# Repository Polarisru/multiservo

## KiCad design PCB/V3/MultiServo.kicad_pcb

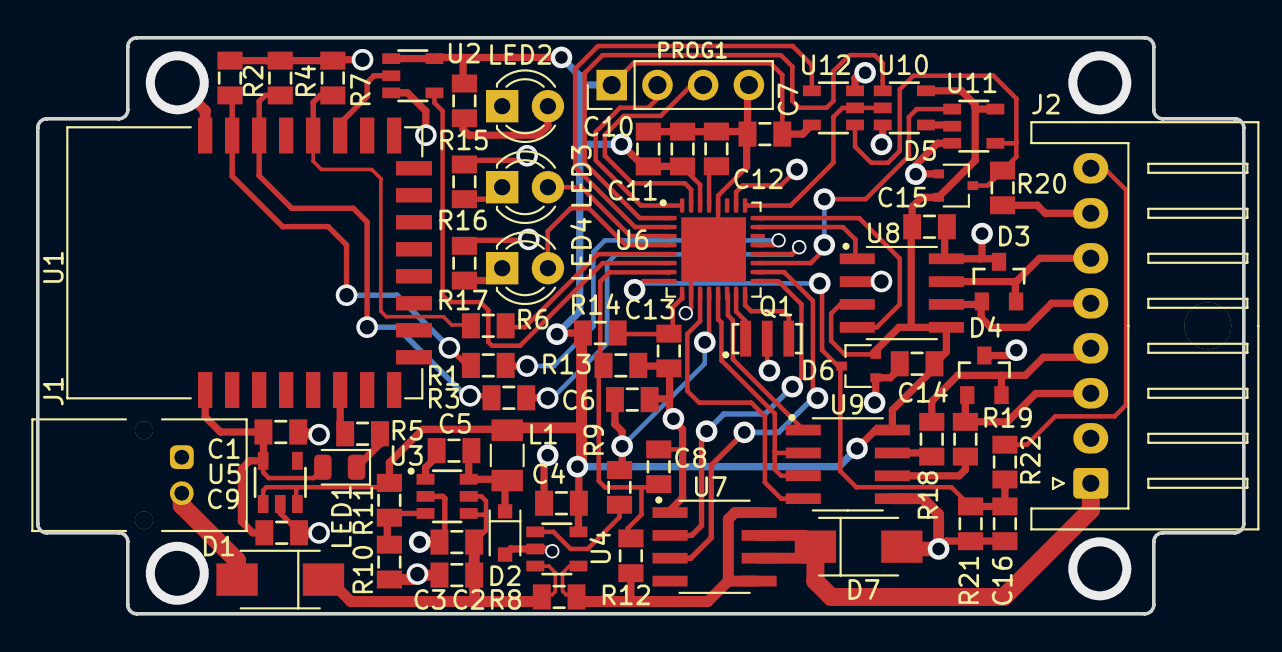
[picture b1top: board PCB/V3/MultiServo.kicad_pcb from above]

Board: 2 copper layers, 67.0 x 32.0 mm, 66 parts (0 on the bottom side), 56 nets.

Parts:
C1, C10, C12, C13: 1.0; C0805
C2: 2.2; C0805
C3, C4, C5, C6, C8, C11, C14, C15, C16: 0.1; C0805
C7, C9: 22.0; C0805
D1: VSSAF5L45; D_SMA
D2: BAT165; D_SOD-323
D3, D4: NUP2105L; SOT23-3
D5, D6: BAT54SW; SOT-323_SC-70
D7: SMA6F30A; D_SMA
J1: JST_S02B_PASK; JST_S02B-PASK-2LFSN_1x02
J2: S08B-XASK-1; JST_XA_S08B-XASK-1x08_P2.50mm_Horizontal
L1: 10uH; L_1206
LED1: RED; LED_0805_2012Metric
LED2: GREEN; LED_D3.0mm
LED3: BLUE; LED_D3.0mm
LED4: RED; LED_D3.0mm
PROG1: 01x04; PinHeader_1x04_P2.54mm_Vertical
Q1: 16MHz; RES-3
R1, R3, R5, R6, R9, R15, R16, R17, R20: 1k; R0805
R2, R4, R7: 2k; R0805
R8: 0.02; R0805
R10: 4k3; R0805
R11: 22k; R0805
R12: 100k; R0805
R13: 15k; R0805
R14: 10; R0805
R18, R19: 100; R0805
R21, R22: 10k; R0805
U1: JDY-08
U2, U11: SN74LV1T126; SOT23-5
U3: MP2459; SOT23-6
U4: INA195A; SOT23-5
U5: MIC5504-3.3; SOT23-5
U6: ATSAMC21E18A-MUT; QFN-32-1EP_5x5mm_P0.5mm_EP3.6x3.6mm
U7: VN750PS; SOIC-8_3.9x4.9mm_P1.27mm
U8: MCP2542FDT-SN; SOIC-8_3.9x4.9mm_P1.27mm
U9: THVD1500; SOIC-8_3.9x4.9mm_P1.27mm
U10, U12: SN74LVC1G86; SOT23-5

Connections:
+3V3: C1.1, C9.2, LED1.2, U1.1, U5.5
+5V: C4.2, C7.2, C10.1, C11.1, C14.1, C15.1, D5.2, D6.2, L1.2, PROG1.1, R11.1, R14.2, R15.2, U2.1, U2.5, U4.5, U5.1, U5.3, U6.30, U8.3, U8.5, U9.8, U10.5, U11.5, U12.5
/485_A: D4.1, J2.3, R19.1
/485_B: D4.2, J2.4, R18.1
/485_DIR: U6.13, U9.2, U9.3
/485_RX: U6.14, U9.1
/485_TX: U6.11, U9.4
/ADC_FB: C16.2, D6.3, R21.2, R22.2, U6.8
/ADC_I: C6.2, R9.1, U6.12
/ADC_U: C8.2, R12.2, R13.1, U6.7
/BT_RX: U2.4, U6.6
/BT_TX: R6.1, U6.5
/CANH: D3.2, J2.6, U8.7
/CANL: D3.1, J2.5, U8.6
/CAN_RX: U6.24, U8.4
/CAN_TX: U6.23, U8.1
/LED1: LED3.2, U6.3
/LED2: LED4.2, U6.4
/POWER: C2.2, C3.2, D1.1, R8.2, U3.4, U3.5, U4.3
/PWM_FB: J2.8, R22.1
/PWRC: R3.2, U6.20
/RES: R1.2, U6.21
/S.BUS: J2.7, R20.1
/SBUSPOL: U6.25, U10.2, U12.2
/SBUSRX: U6.2, U12.4
/SBUSTE: U6.19, U11.1
/SBUSTX: U6.1, U10.1
/SERVO+: D7.1, J2.1, U7.6, U7.7
/SERVO_ON: U6.17, U7.2
/STATUS: U6.18, U7.3
/SWCLK: PROG1.3, U6.31
/SWDIO: PROG1.2, U6.32
GND: C1.2, C2.1, C3.1, C4.1, C6.1, C7.1, C8.1, C9.1, C10.2, C11.2, C12.2, C13.2, C14.2, C15.2, C16.1, D2.2, D3.3, D4.3, D5.1, D6.1, D7.2, J1.1, J2.2, LED2.1, PROG1.4, Q1.2, R2.1, R4.1, R7.1, R10.2, R13.2, R16.1, R17.1, R21.1, U1.24, U2.3, U3.2, U4.2, U5.2, U6.10, U6.28, U6.EP, U7.1, U8.2, U8.8, U9.5, U10.3, U11.3, U12.3
unnamed: C5.1, U3.1
unnamed: C5.2, D2.1, L1.1, U3.6
unnamed: C12.1, U6.29
unnamed: C13.1, R14.1, U6.9
unnamed: D1.2, J1.2
unnamed: D5.3, R20.2, U11.4, U12.1
unnamed: LED1.1, R5.1
unnamed: LED2.2, R15.1
unnamed: LED3.1, R16.2
unnamed: LED4.1, R17.2
unnamed: Q1.1, U6.15
unnamed: Q1.3, U6.16
unnamed: R1.1, R2.2, U1.23
unnamed: R3.1, R4.2, U1.22
unnamed: R5.2, U1.6
unnamed: R6.2, R7.2, U1.20
unnamed: R9.2, U4.1
unnamed: R10.1, R11.2, U3.3
unnamed: R8.1, R12.1, U4.4, U7.5, U7.8
unnamed: R18.2, U9.7
unnamed: R19.2, U9.6
unnamed: U1.19, U2.2
unnamed: U10.4, U11.2

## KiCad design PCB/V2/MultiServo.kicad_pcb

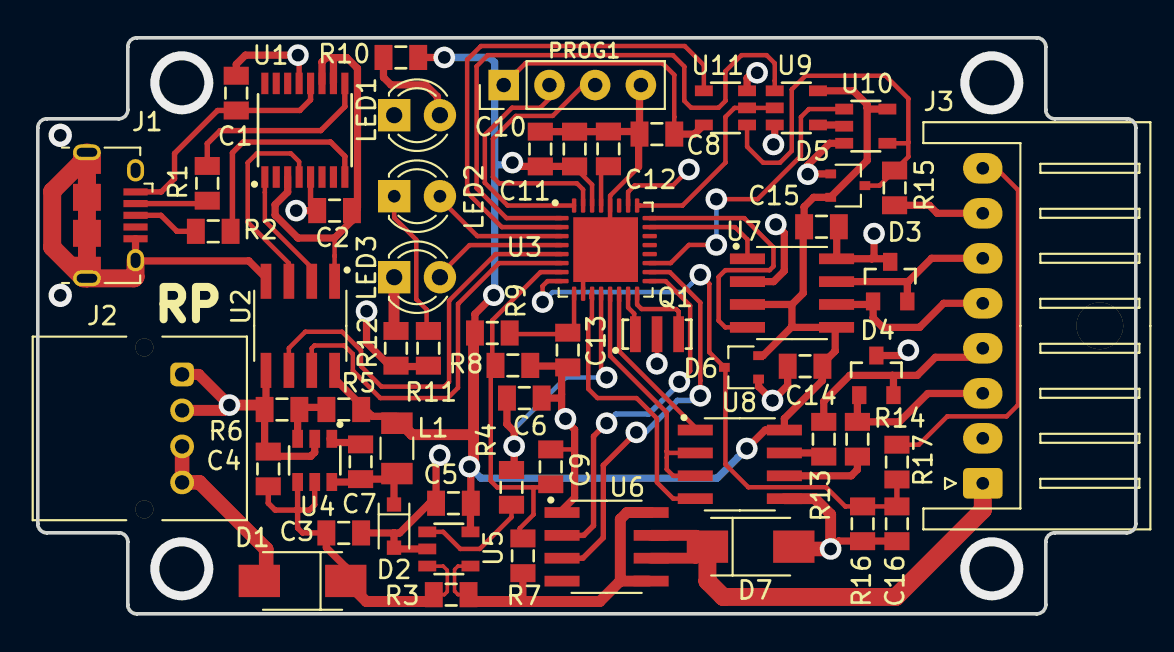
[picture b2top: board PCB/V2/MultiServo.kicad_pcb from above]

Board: 2 copper layers, 61.0 x 32.0 mm, 60 parts (0 on the bottom side), 56 nets.

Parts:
C1, C3: 2.2; C0805
C2, C10, C12, C13: 1.0; C0805
C4, C5, C6, C7, C9, C11, C14, C15, C16: 0.1; C0805
C8: 22.0; C0805
D1: VSSAF5L45; D_SMA
D2: BAT165; D_SOD-323
D3, D4: NUP2105L; SOT23-3
D5, D6: BAT54SW; SOT-323_SC-70
D7: SMA6F30A; D_SMA
J1: USB_B_Micro; USB_Micro-B_Amphenol_10118194_Horizontal
J2: S04B; JST_S04B-PASK-2LFSN_1x04
J3: S08B-XASK-1; JST_XA_S08B-XASK-1x08_P2.50mm_Horizontal
L1: 10uH; L_1206
LED1: GREEN; LED_D3.0mm
LED2: BLUE; LED_D3.0mm
LED3: RED; LED_D3.0mm
PROG1: 01x04; PinHeader_1x04_P2.54mm_Vertical
Q1: 16MHz; RES-3
R1, R2: 27; R0805
R3: 0.02; R0805
R4, R10, R11, R12, R15: 1k; R0805
R5: 22k; R0805
R6: 4k3; R0805
R7: 100k; R0805
R8: 15k; R0805
R9: 10; R0805
R13, R14: 100; R0805
R16, R17: 10k; R0805
U1: FT230XS; SSOP-16_3.9x4.9mm_P0.635mm
U2: Si8621BC; SOIC-8_3.9x4.9mm_P1.27mm
U3: ATSAMC21E18A-MUT; QFN-32-1EP_5x5mm_P0.5mm_EP3.6x3.6mm
U4: MP2459; SOT23-6
U5: INA195A; SOT23-5
U6: VN750PS; SOIC-8_3.9x4.9mm_P1.27mm
U7: MCP2542FDT-SN; SOIC-8_3.9x4.9mm_P1.27mm
U8: THVD1500; SOIC-8_3.9x4.9mm_P1.27mm
U9, U11: SN74LVC1G86; SOT23-5
U10: SN74LV1T126; SOT23-5

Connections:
+5V: C5.2, C8.2, C10.1, C11.1, C14.1, C15.1, D5.2, D6.2, L1.2, PROG1.1, R5.1, R9.2, R10.2, U2.8, U3.30, U5.5, U7.3, U7.5, U8.8, U9.5, U10.5, U11.5
/485_A: D4.1, J3.3, R14.1
/485_B: D4.2, J3.4, R13.1
/485_DIR: U3.13, U8.2, U8.3
/485_RX: U3.14, U8.1
/485_TX: U3.11, U8.4
/ADC_FB: C16.2, D6.3, R16.2, R17.2, U3.8
/ADC_I: C6.2, R4.1, U3.12
/ADC_U: C9.2, R7.2, R8.1, U3.7
/CANH: D3.2, J3.6, U7.7
/CANL: D3.1, J3.5, U7.6
/CAN_RX: U3.24, U7.4
/CAN_TX: U3.23, U7.1
/LED1: LED2.2, U3.3
/LED2: LED3.2, U3.4
/POWER: C3.2, C4.2, D1.1, R3.2, U4.4, U4.5, U5.3
/PWM_FB: J3.8, R17.1
/S.BUS: J3.7, R15.1
/SBUSPOL: U3.25, U9.2, U11.2
/SBUSRX: U3.2, U11.4
/SBUSTE: U3.19, U10.1
/SBUSTX: U3.1, U9.1
/SERVO+: D7.1, J3.1, U6.6, U6.7
/SERVO_ON: U3.17, U6.2
/STATUS: U3.18, U6.3
/SWCLK: PROG1.3, U3.31
/SWDIO: PROG1.2, U3.32
/USB_GND: C1.1, C2.2, J1.5, J1.6, U1.5, U1.13, U2.4
/USB_RX: U2.7, U3.6
/USB_TX: U2.6, U3.5
GND: C3.1, C4.1, C5.1, C6.1, C8.1, C9.1, C10.2, C11.2, C12.2, C13.2, C14.2, C15.2, C16.1, D2.2, D3.3, D4.3, D5.1, D6.1, D7.2, J2.1, J2.2, J3.2, LED1.1, PROG1.4, Q1.2, R6.2, R8.2, R11.1, R12.1, R16.1, U2.5, U3.10, U3.28, U3.EP, U4.2, U5.2, U6.1, U7.2, U7.8, U8.5, U9.3, U10.3, U11.3
unnamed: C1.2, J1.1, U1.12
unnamed: C2.1, U1.3, U1.10, U1.11, U2.1
unnamed: C7.1, U4.1
unnamed: C7.2, D2.1, L1.1, U4.6
unnamed: C12.1, U3.29
unnamed: C13.1, R9.1, U3.9
unnamed: D1.2, J2.3, J2.4
unnamed: D5.3, R15.2, U10.4, U11.1
unnamed: J1.2, R1.2
unnamed: J1.3, R2.2
unnamed: LED1.2, R10.1
unnamed: LED2.1, R11.2
unnamed: LED3.1, R12.2
unnamed: Q1.1, U3.15
unnamed: Q1.3, U3.16
unnamed: R1.1, U1.9
unnamed: R2.1, U1.8
unnamed: R3.1, R7.1, U5.4, U6.5, U6.8
unnamed: R4.2, U5.1
unnamed: R5.2, R6.1, U4.3
unnamed: R13.2, U8.7
unnamed: R14.2, U8.6
unnamed: U1.1, U2.2
unnamed: U1.4, U2.3
unnamed: U9.4, U10.2

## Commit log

2020-12-20 New modules added from SPAN, compilation successful, but many functions need to be updated
2020-12-22 KeeLoq is not working yet
2020-12-22 Schematics is new
2020-12-22 Software for bootloading added (Lazarus) Bootloader from LS1 project added, must be changed for ATSAMC21 Keeloq receiving via TCC capture is working, but must be improved for real life
2020-12-23 PWM is working, Analog module started, outputs working, communication working
2020-12-23 Working on RS485 and CAN
2020-12-28 RS485 servo is supported EEPROM settings are working Bootloader is working
2020-12-31 KeeLoq is working now CAN is also working
2021-01-01 3D models added Supply voltage and current calibration are working Problem with voltage measurement fixed Updater is working
2021-01-01 pyVisio directory added
2021-01-02 Connection, position, readout of U/I/t° is working ToDo: Read parameters, check for bugs
2021-01-03 Write/read parameters is not ready
2021-01-03 main.py added
2021-01-03 Generated Hex file added to repository
2021-01-18 feat: Channels for ADC added, current is ADC1 now
2021-01-19 ADC DMA added Drivers moved to drivers.h
2021-01-20 Working on SBUS
2021-01-22 PCBs added for both USB and BT
2021-01-31 Futaba is working now, but additional thread is needed. Fast analog channel with DMA is working now. Some new HW files added.
2021-02-01 Current graph readout added (GBx) Graph added to pyvisio
2021-02-02 FFT added to current graph
2021-02-03 SBUS has own task and transferred via DMA
2021-02-04 Libcanard added Full SBUS support now Problem with ADC0 solved, but needs to be cleared
2021-02-16 - Meteor protocol started - UAVCAN v0 files added - PWM frequency is 100Hz now - FFT added, but not working properly
2021-02-24 3d model for bottom changed for new PCB
2021-02-24 3d model for new PCB added
2021-02-24 3d model for cover added for new PCB
2021-02-28 HW: Cover changed to fix LEDs position
2021-03-02 FW: - Simple JDY-08 initialization implemented, no settings yet - Baudrate settings added to RS232 module
2021-03-02 FW: - Added name to JDY-08 HW: - Bottom for MS_BT prepared
2021-03-03 FW: - Bluetooth set name processing improved - Another LED is blinking now (blue)
2021-03-03 HW: - Bluetooth bottom and cover added for 3D-printing
2021-03-07 FW: - New CAN protocol added - New command added to set bus ID: SID
2021-03-20 FW: - serial channel module added (PWM bootloader) - bootloader changed - new CAN protocol must work now - SID command added to set ID for bus communication
2021-03-21 FW: - Bootloader is activated now, but not everything is tested
2021-03-22 FW: - Working on bootloader functionality
2021-03-23 FW: - CAN bootloader function improved
2021-03-24 FW: - bootloader is working now
2021-03-29 FW: - PWM/RS485/CAN bootloader is working - Some bugs fixed in communication protocols for bootloader HW: - LEDs size increased for cover
2021-04-30 Meteor support started
2021-05-02 FW: - Some more Meteor functions
2021-05-19 FW: - More Meteor support
